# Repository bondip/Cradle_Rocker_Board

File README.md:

# Cradle_Rocker_Board
This repository contains the design files for the cradle rocker board and electronics

## Notes
2xhall effect sensors
1xlow speed high torque DC motor
potentiometer for modifiying torque
potentiometer for modifying delay
microcontroller
dc power supply

Firmware note:

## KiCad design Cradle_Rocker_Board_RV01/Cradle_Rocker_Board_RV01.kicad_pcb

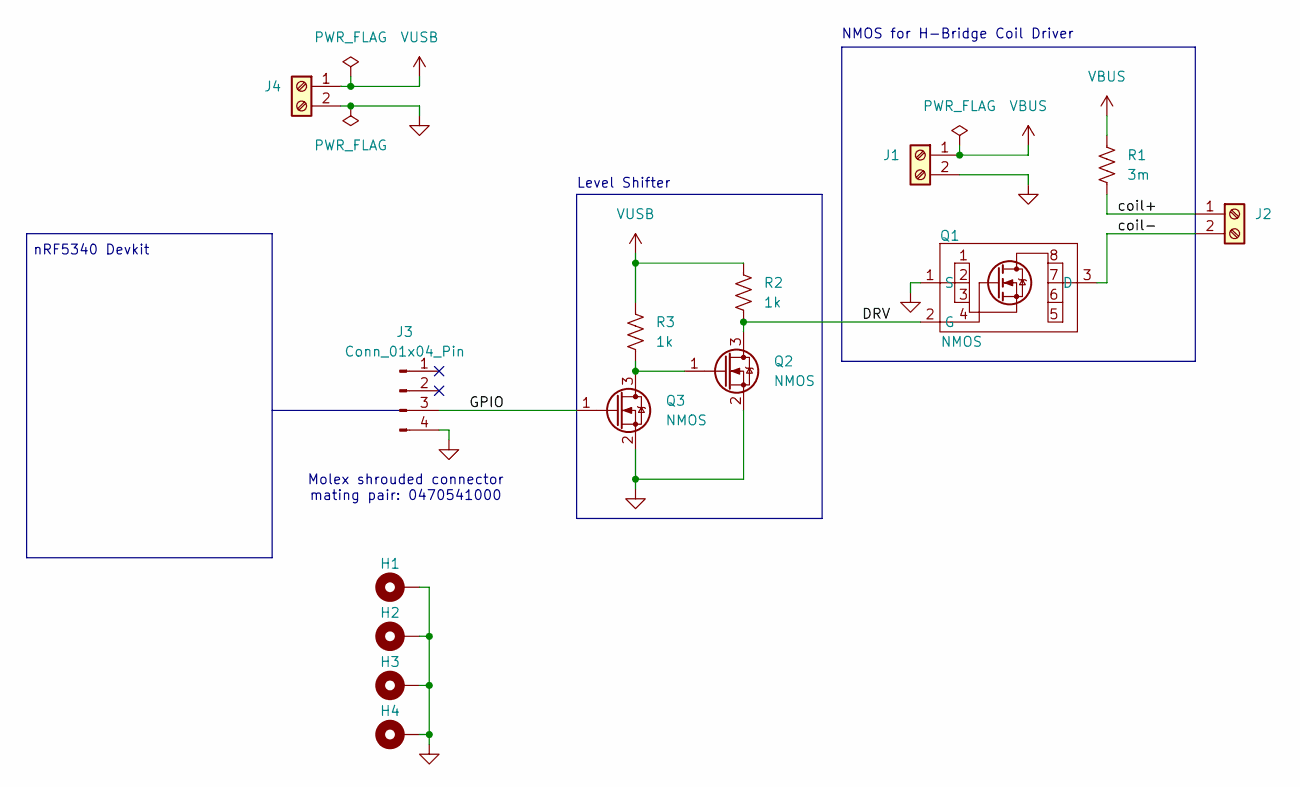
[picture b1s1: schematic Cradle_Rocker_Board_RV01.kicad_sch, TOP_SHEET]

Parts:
H1, H2, H3, H4: MountingHole_Pad; MountingHole_3.2mm_M3_DIN965_Pad
J1, J2, J4: Screw_Terminal_01x02; 1984617_PHOENIX; ManufacturerPN 1984617
J3: Conn_01x04_Pin; 47053-1000_MOL; ManufacturerPN 0470531000
Q1: NMOS; BSC014N04LSIATMA1; ManufacturerPN BSC010N04LSIATMA1
Q2, Q3: NMOS; DIO_RB558WMF_ROM-L; ManufacturerPN RE1C002UNTCL
R1: 3m; WSHP28183L000FEA_Vishay_Dale; ManufacturerPN WSHP28183L000FEA
R2, R3: 1k; R0603; ManufacturerPN ERJ-3EKF1001V

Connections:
/DRV: Q1.2 (G), Q2.3 (D), R2.2
/GPIO: J3.3, Q3.1 (G)
/coil+: J2.1, R1.2
/coil-: J2.2, Q1.3 (D)
GND: H1.1, H2.1, H3.1, H4.1, J1.2, J3.4, J4.2, Q1.1 (S), Q2.2 (S), Q3.2 (S)
unnamed: Q2.1 (G), Q3.3 (D), R3.2
VBUS: J1.1, R1.1
VUSB: J4.1, R2.1, R3.1

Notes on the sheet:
nRF5340 Devkit
NMOS for H-Bridge Coil Driver
Molex shrouded connector mating pair: 0470541000
Level Shifter

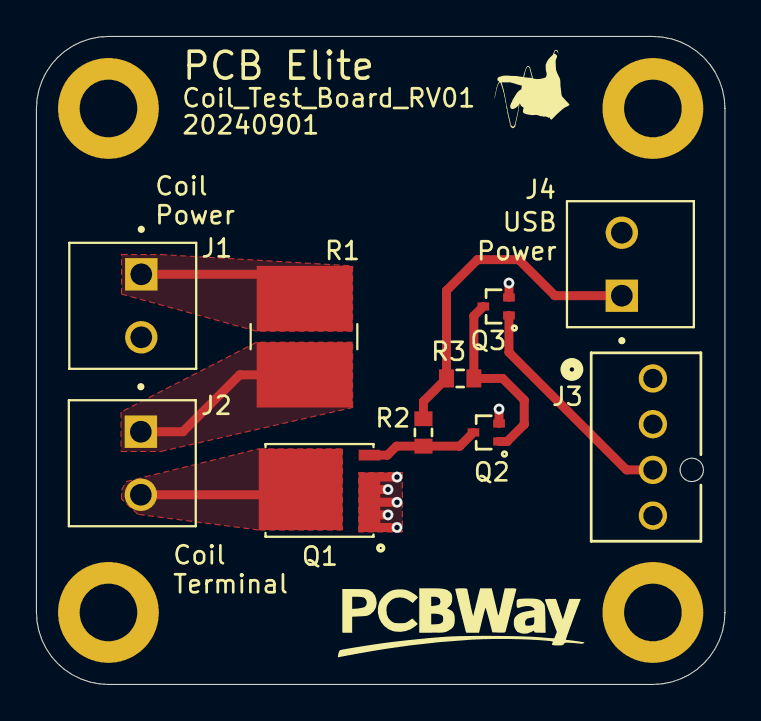
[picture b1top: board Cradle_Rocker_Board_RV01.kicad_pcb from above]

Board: 2 copper layers, 38.2 x 36.0 mm, 14 parts (0 on the bottom side), 8 nets.

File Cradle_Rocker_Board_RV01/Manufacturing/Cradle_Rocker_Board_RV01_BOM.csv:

"Reference","Value","Qty","Manufacturer","ManufacturerPN"
"J1,J2,J4","Screw_Terminal_01x02","3","Phoenix Contact","1984617"
"J3","Conn_01x04_Pin","1","Molex","0470531000"
"Q1","NMOS","1","Infineon Technologies","BSC010N04LSIATMA1"
"Q2,Q3","NMOS","2","Rohm Semiconductor","RE1C002UNTCL"
"R1","3m","1","Vishay Dale","WSHP28183L000FEA"
"R2,R3","1k","2","Panasonic Electronic Components","ERJ-3EKF1001V"

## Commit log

2024-08-31 First Version of the Schematics Complete
2024-09-02 This is actually just a coil test board.
    Submitted RV01 to PCBWay for Fabrication and Assembly on 20240902
2024-09-02 Working Blinky FW
2024-09-04 Working Button + LED ISR Example FW
2024-09-08 Added arduino code for GPIO testing
2024-12-15 Added mechanical and backups
